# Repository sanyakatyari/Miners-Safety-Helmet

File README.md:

# Miners-Safety-Helmet

An IoT-based wearable safety helmet designed to enhance underground miner safety
through multi-sensor hazard detection, real-time audio-visual alerts, and cloud 
telemetry via ThingSpeak.

------------------------------------------------------------------------------
TABLE OF CONTENTS
------------------------------------------------------------------------------
1. Overview & Objectives
2. Key Features
3. Hardware Architecture & Components
4. Firmware & Software Details
5. Pin Mapping & Circuitry
6. System Workflow & Hazard Logic
7. PCB Design & Hardware Layout
8. Installation & Setup Guide
9. Testing & Validation Results
10. Future Enhancements
11. Project Team & Acknowledgments
12. References

------------------------------------------------------------------------------
1. OVERVIEW & OBJECTIVES
------------------------------------------------------------------------------
Underground mining involves extreme working conditions where hazardous gas leaks,
high temperature/humidity, sudden impacts/falls, and low overhead clearance pose
severe threats to human life. 

Objectives:
- Provide clear, immediate audio-visual alerts (buzzer chimes & flashing LED) 
  tailored for all workers, including illiterate miners.
- Integrate multi-sensor environmental and motion monitoring into a lightweight,
  wearable, low-cost helmet.
- Deliver real-time cloud data logging via ThingSpeak for supervisory oversight
  and remote safety management.

------------------------------------------------------------------------------
2. KEY FEATURES
------------------------------------------------------------------------------
- Environmental Sensing: High-accuracy temperature and humidity monitoring.
- Combustible Gas Detection: Real-time monitoring of dangerous gas/smoke levels.
- Motion & Impact Tracking: IMU-based 6-axis accelerometer and gyroscope tracking
  with complementary filtering to detect sudden tilts or impacts.
- Overhead Clearance Warnings: Ultrasonic distance detection to warn of low ceiling 
  hazards in tight shafts.
- Accessible Audio-Visual Alarms: High-frequency buzzer tones and blinking LED patterns.
- Manual SOS & Reset Controls: Tactile push-buttons for manual emergency activation 
  and alert reset with software debouncing.
- IoT Cloud Telemetry: Automatic Wi-Fi data upload to ThingSpeak every 15 seconds.

------------------------------------------------------------------------------
3. HARDWARE ARCHITECTURE & COMPONENTS
------------------------------------------------------------------------------
- Microcontroller: Espressif ESP32-S3 WROOM / ESP32 Development Board
  (Integrated Wi-Fi, ADC channels, native I2C support)
- Temperature & Humidity Sensor: DHT22 (Precision digital sensor)
- Combustible Gas Sensor: MQ-2 Gas Module (Smoke, CO, LPG detection)
- Motion & Inertial Sensor: MPU6050 6-Axis IMU (Accelerometer + Gyroscope)
- Proximity / Distance Sensor: HC-SR04 Ultrasonic Sensor
- Alert Outputs: Active Piezo Buzzer & High-Brightness LED
- Manual Controls: 2x Tactile Push-Buttons (Trigger SOS / Reset)
- Power Management: Rechargeable Battery Module & LDO Voltage Regulator

------------------------------------------------------------------------------
4. FIRMWARE & SOFTWARE DETAILS
------------------------------------------------------------------------------
- Language / Framework: C++ / Arduino Framework for ESP32
- Key Libraries:
  * WiFi.h & Wire.h (ESP32 Built-in)
  * ThingSpeak.h (ThingSpeak Communication)
  * DHT.h (Adafruit DHT Sensor Library)
  * Adafruit_MPU6050.h & Adafruit_Sensor.h (Adafruit MPU6050 Driver)

Data Filter Algorithm:
- Complementary Filter applied to MPU6050 readings:
  tiltDeg = 0.98 * gyroTilt + 0.02 * accelTilt
  (Distinguishes dynamic jerk/vibration from sustained tilt/impacts).

------------------------------------------------------------------------------
5. PIN MAPPING & CIRCUITRY
------------------------------------------------------------------------------
Component           | Module Pin | ESP32 GPIO / Pin Code
--------------------|------------|----------------------
DHT22 Temp/Hum      | DATA       | GPIO 2 (D0)
MQ-2 Gas Sensor     | AOUT       | GPIO 3 (D1 / ADC1)
Piezo Buzzer        | Positive   | GPIO 8 (D8)
Status LED          | Anode      | GPIO 10 (D10)
Manual Trigger SOS  | Pin        | GPIO 5 (D3 - INPUT_PULLUP)
Alarm Reset Button  | Pin        | GPIO 9 (D9 - INPUT_PULLUP)
HC-SR04 Ultrasonic  | TRIG       | GPIO 4 (D2)
HC-SR04 Ultrasonic  | ECHO       | GPIO 6 (D4)
MPU6050 IMU         | SDA        | GPIO 6 (D4)
MPU6050 IMU         | SCL        | GPIO 7 (D5)

------------------------------------------------------------------------------
6. SYSTEM WORKFLOW & HAZARD LOGIC
------------------------------------------------------------------------------
Sensors are sampled every 500ms. An alarm state triggers if ANY of the 
following thresholds are exceeded:

Parameter              | Threshold Level
-----------------------|------------------------------------
Temperature            | > 35.0 °C
Humidity               | > 80.0 %
Gas Concentration      | > 1800 Raw ADC Value
Tilt Angle             | > 50.0 Degrees
Overhead Clearance     | < 30.0 cm ( sustained for > 30 mins )
Manual SOS Trigger     | Button Pressed (LOW)

Cloud Upload:
- Upload Interval: Every 15 seconds to ThingSpeak.
- Fields Map:
  Field 1: Temperature (°C)
  Field 2: Humidity (%)
  Field 3: Gas Raw Reading
  Field 4: Calculated Tilt Angle (Degrees)
  Field 5: Clearance Distance (cm)
  Field 6: Hazard Alarm State (1 = Active, 0 = Normal)
  Field 7: Manual Alarm State (1 = Active, 0 = Off)

------------------------------------------------------------------------------
7. PCB DESIGN & HARDWARE LAYOUT
------------------------------------------------------------------------------
- Two-layer custom PCB designed using Altium Designer / KiCad.
- Features solid ground plane pour on top and bottom layers for noise immunity.
- Short I2C traces to avoid clock jitter and signal attenuation.
- Isolated high-frequency/noisy routing from analog sensor traces.
- Keep-out zone maintained under ESP32 PCB antenna to optimize Wi-Fi range.

------------------------------------------------------------------------------
8. INSTALLATION & SETUP GUIDE
------------------------------------------------------------------------------
1. Prerequisites:
   - Install Arduino IDE (v2.0 or higher recommended).
   - Install ESP32 Board Manager core in Arduino IDE.
   - Install required libraries: `DHT sensor library`, `Adafruit MPU6050`, 
     `Adafruit Unified Sensor`, `ThingSpeak`.

2. Configuration:
   - Open `miner_safety_helmet.ino`.
   - Update Wi-Fi Credentials:
     const char* ssid = "YOUR_WIFI_SSID";
     const char* password = "YOUR_WIFI_PASSWORD";
   - Update ThingSpeak Credentials:
     unsigned long channelID = YOUR_CHANNEL_ID;
     const char* writeAPIKey = "YOUR_WRITE_API_KEY";

3. Uploading Firmware:
   - Connect ESP32 board via USB.
   - Select correct COM Port and Board model (e.g., ESP32 Dev Module / ESP32-S3).
   - Compile and upload the sketch.

------------------------------------------------------------------------------
9. TESTING & VALIDATION RESULTS
------------------------------------------------------------------------------
- Environmental Chamber Testing: Successfully triggered alerts at > 35°C and 
  elevated smoke exposure.
- Motion Simulation: Complementary filter correctly filtered high-frequency 
  jerks while catching sustained tilt (>50°).
- Distance Validation: Accurate proximity alerts up to 30 cm clearance limit.
- Cloud Integration: Continuous 24-hour test verified 99.8% successful payload 
  delivery to ThingSpeak.

------------------------------------------------------------------------------
12. REFERENCES
------------------------------------------------------------------------------
- IEEE Xplore: "IoT-Enabled Safety Helmet for Coal Miners" 
  (https://ieeexplore.ieee.org/document/10561018/)
- KSCST Project Reports: "An IoT Based Smart Helmet for Industrial And Mining Workers"
- IJRASET: "IOT Mining Tracking & Worker Safety Helmet" (2024)
- Random Nerd Tutorials: "ESP32 Publish Sensor Readings to ThingSpeak"
==============================================================================

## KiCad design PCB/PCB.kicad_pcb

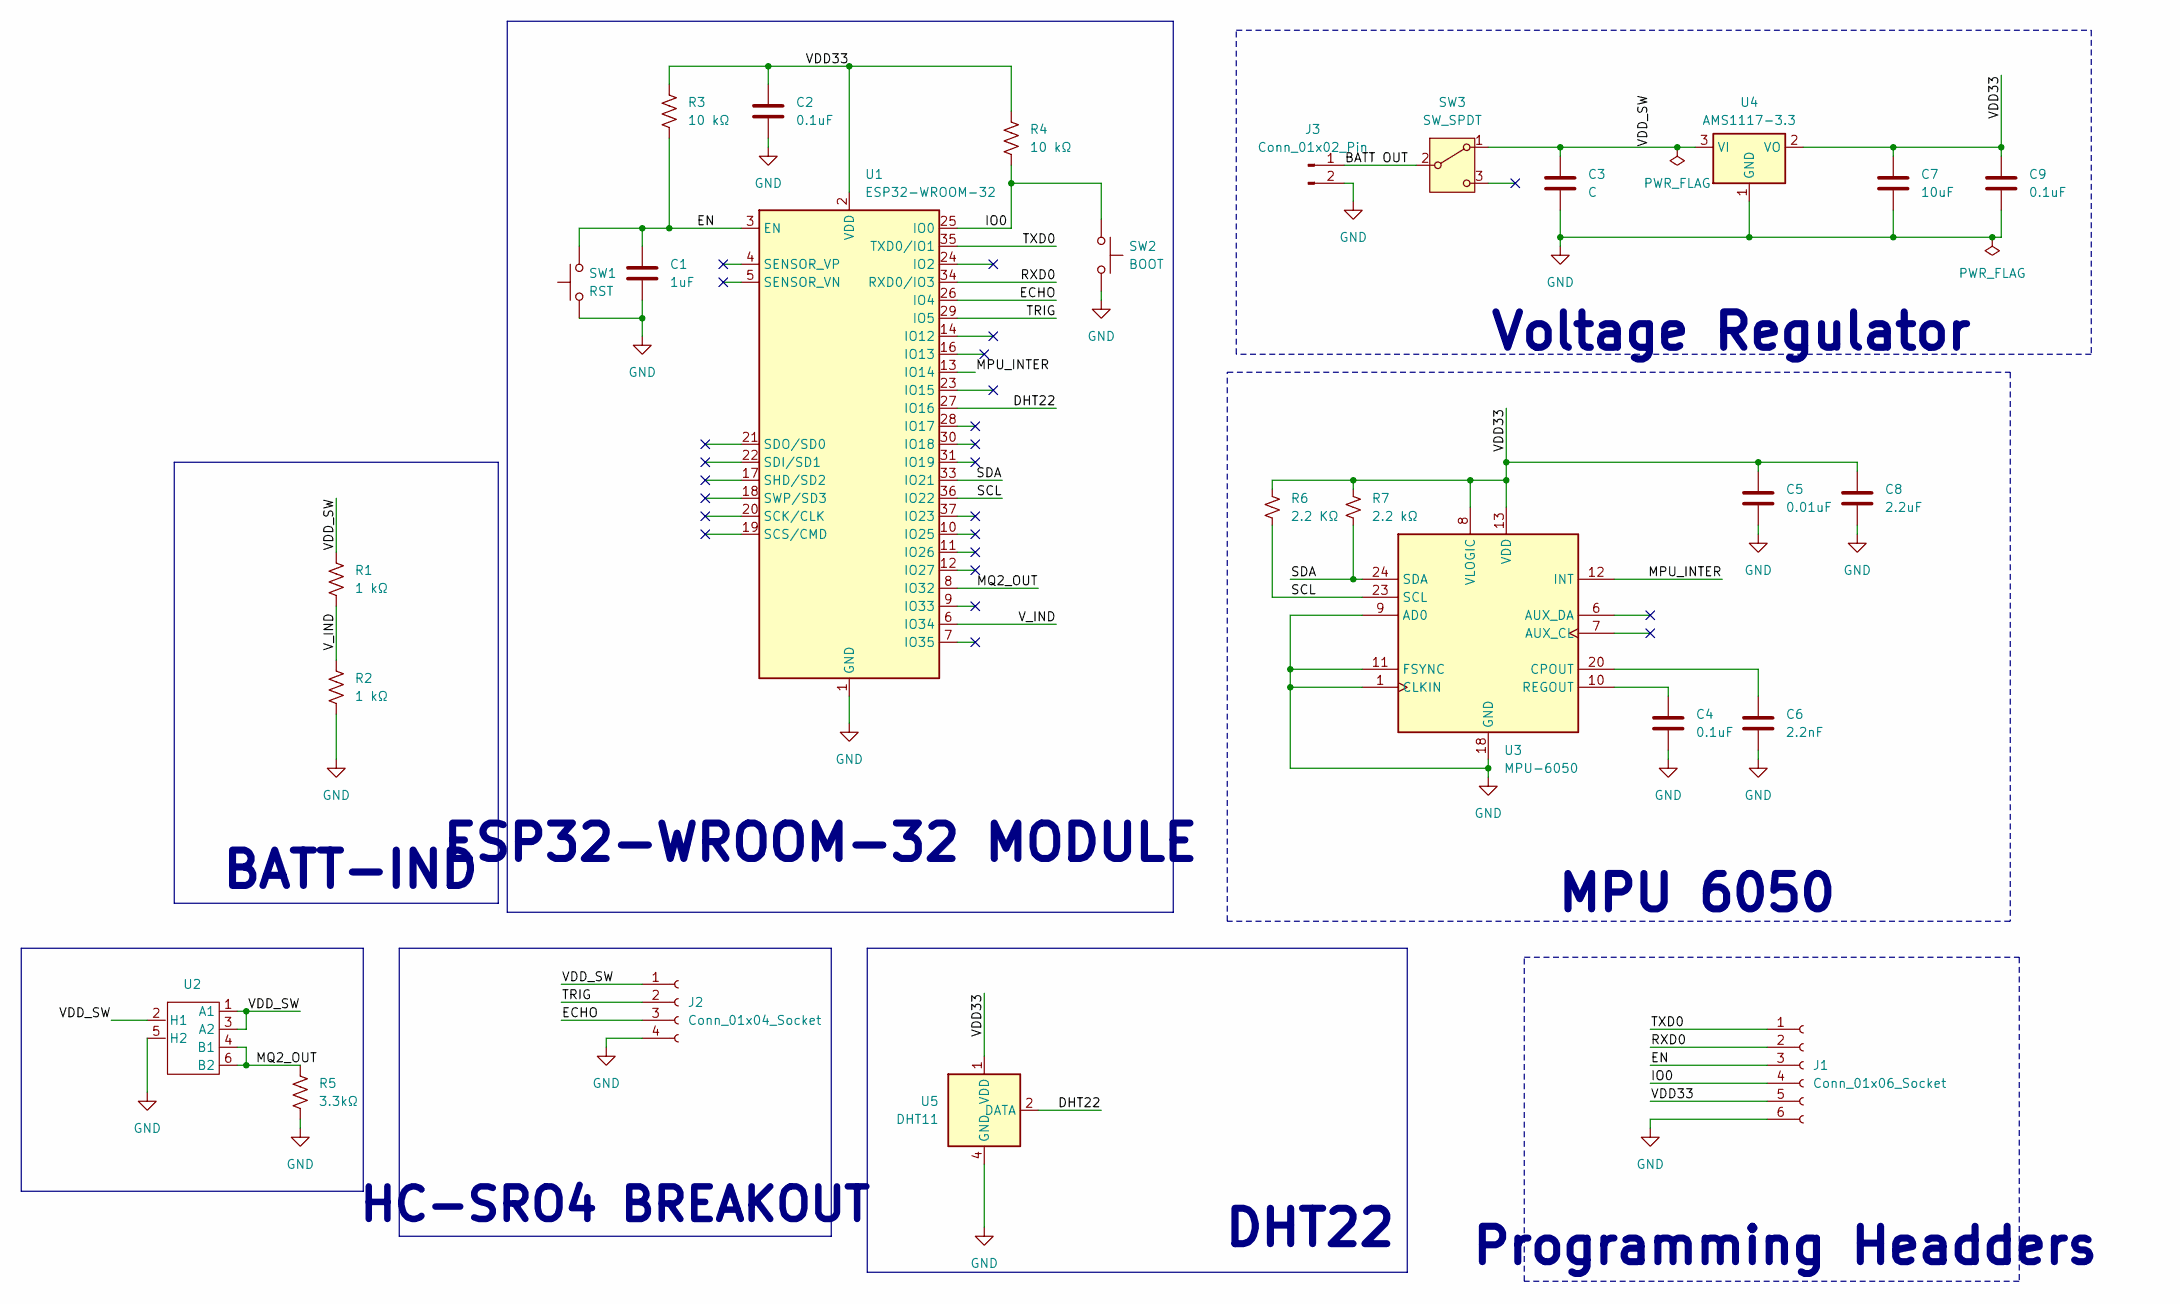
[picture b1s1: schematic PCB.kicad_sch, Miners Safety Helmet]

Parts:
C1: 1uF; C_Disc_D3.0mm_W1.6mm_P2.50mm
C2, C4, C9: 0.1uF; C_Disc_D3.0mm_W1.6mm_P2.50mm
C3: C; C_Disc_D3.0mm_W1.6mm_P2.50mm
C5: 0.01uF; C_Disc_D3.0mm_W1.6mm_P2.50mm
C6: 2.2nF; C_Disc_D3.0mm_W1.6mm_P2.50mm
C7: 10uF; C_Disc_D3.0mm_W1.6mm_P2.50mm
C8: 2.2uF; C_Disc_D3.0mm_W1.6mm_P2.50mm
J1: Conn_01x06_Socket; PinHeader_1x06_P2.54mm_Vertical
J2: Conn_01x04_Socket; PinHeader_1x04_P2.54mm_Vertical
J3: Conn_01x02_Pin; PinHeader_1x02_P2.54mm_Vertical
R1, R2: 1 kΩ; R_Axial_DIN0207_L6.3mm_D2.5mm_P10.16mm_Horizontal
R3, R4: 10 kΩ; R_Axial_DIN0207_L6.3mm_D2.5mm_P10.16mm_Horizontal
R5: 3.3kΩ; R_Axial_DIN0207_L6.3mm_D2.5mm_P10.16mm_Horizontal
R6: 2.2 KΩ; R_Axial_DIN0207_L6.3mm_D2.5mm_P2.54mm_Vertical
R7: 2.2 kΩ; R_Axial_DIN0207_L6.3mm_D2.5mm_P2.54mm_Vertical
SW1: RST; SW_PUSH_6mm
SW2: BOOT; SW_PUSH_6mm
SW3: SW_SPDT; SW_Slide_SPDT_Straight_CK_OS102011MS2Q
U1: ESP32-WROOM-32
U2: MQ2
U3: MPU-6050; InvenSense_QFN-24_4x4mm_P0.5mm
U4: AMS1117-3.3; SOT-223-3_TabPin2
U5: DHT11; Aosong_DHT11_5.5x12.0_P2.54mm

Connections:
/BATT OUT: J3.1, SW3.2 (B)
/DHT22: U1.27 (IO16), U5.2 (DATA)
/ECHO: J2.3, U1.26 (IO4)
/EN: C1.1, J1.3, R3.1, SW1.2, U1.3 (EN)
/IO0: J1.4, R4.1, SW2.1, U1.25 (IO0)
/MPU_INTER: U1.13 (IO14), U3.12 (INT)
/MQ2_OUT: R5.2, U1.8 (IO32), U2.4 (B1), U2.6 (B2)
/RXD0: J1.2, U1.34 (RXD0/IO3)
/SCL: R6.2, U1.36 (IO22), U3.23 (SCL)
/SDA: R7.2, U1.33 (IO21), U3.24 (SDA)
/TRIG: J2.2, U1.29 (IO5)
/TXD0: J1.1, U1.35 (TXD0/IO1)
/VDD33: C2.1, C5.1, C7.1, C8.1, C9.1, J1.5, R3.2, R4.2, R6.1, R7.1, U1.2 (VDD), U3.8 (VLOGIC), U3.13 (VDD), U4.2 (VO), U5.1 (VDD)
/VDD_SW: C3.1, J2.1, R1.2, SW3.1 (A), U2.1 (A1), U2.2 (H1), U2.3 (A2), U4.3 (VI)
/V_IND: R1.1, R2.2, U1.6 (IO34)
GND: C1.2, C2.2, C3.2, C4.2, C5.2, C6.2, C7.2, C8.2, C9.2, J1.6, J2.4, J3.2, R2.1, R5.1, SW1.1, SW2.2, U1.1 (GND), U1.15 (GND), U1.38 (GND), U1.39 (GND), U2.5 (H2), U3.1 (CLKIN), U3.9 (AD0), U3.11 (FSYNC), U3.18 (GND), U4.1 (GND), U5.4 (GND)
unnamed: C6.1, U3.20 (CPOUT)
unnamed: C4.1, U3.10 (REGOUT)

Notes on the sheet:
HC-SRO4 BREAKOUT
BATT-IND
DHT22
Programming Headders
ESP32-WROOM-32 MODULE
Voltage Regulator
MPU 6050

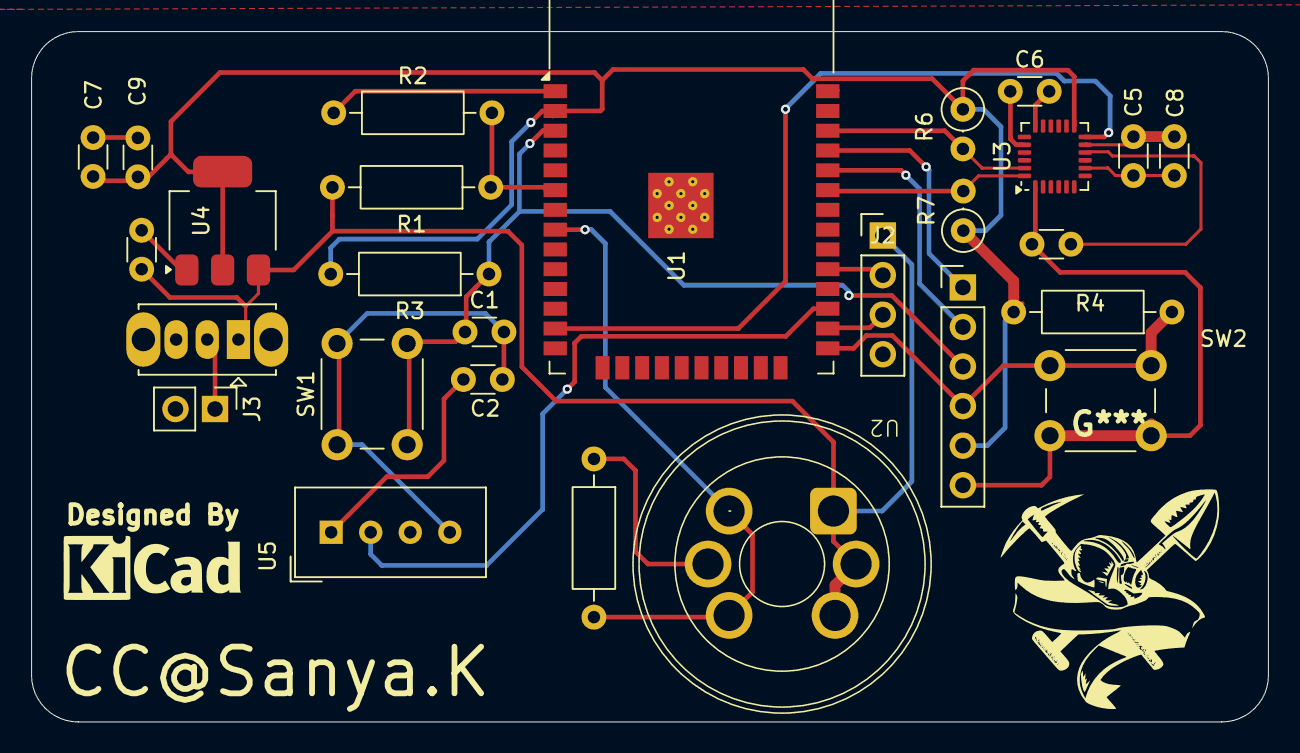
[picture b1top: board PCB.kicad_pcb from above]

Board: 2 copper layers, 79.4 x 44.3 mm, 27 parts (0 on the bottom side), 18 nets.
